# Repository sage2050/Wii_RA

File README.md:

Drop Wii_RA gerbers.zip into JLC pcb  

Components:  

U1 - Seeed Studios XIAO ESP32-S3  
https://www.amazon.com/Dual-core-Supported-Efficiency-Interface-Robotics/dp/B0BYSB66S5?sr=8-3

D1 - OnSemi SS14 or similar  
Optional - allows you to safely power the adapter using the memory card slot while maintaining a usb connection  
https://www.digikey.com/en/products/detail/onsemi/SS14/965474

BZ1 - PUIAudio SMT-0540-T-9-R or similar  
Optional - can play a tone when achievements are earned  
https://www.digikey.com/en/products/detail/pui-audio-inc/SMT-0540-T-9-R/13165909

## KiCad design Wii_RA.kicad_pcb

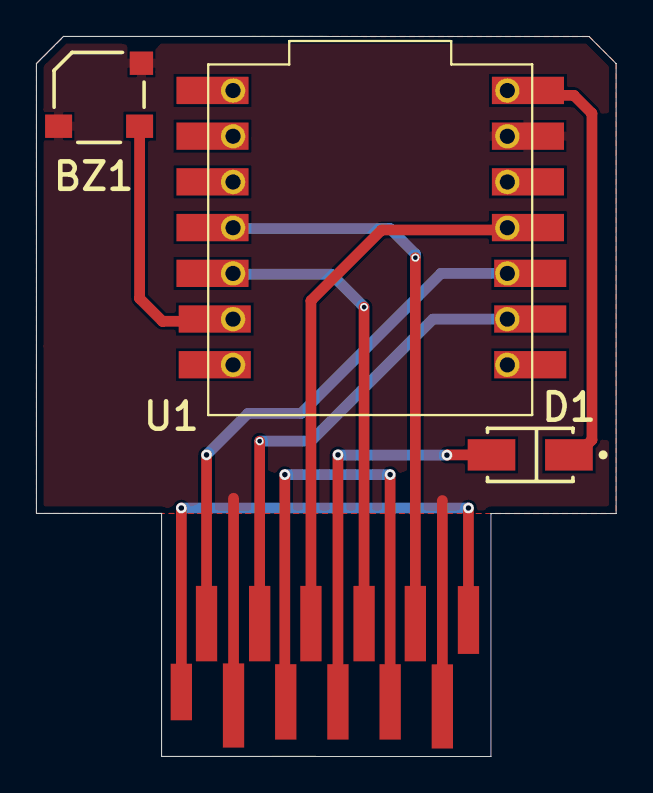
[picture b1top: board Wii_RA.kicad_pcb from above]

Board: 2 copper layers, 32.2 x 40.0 mm, 4 parts (0 on the bottom side), 11 nets.

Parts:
BZ1: SMT-0540-S-R; PUI-SMT-0540-S-R_V
D1: SS14; FP-403AE-MFG
P1: GC_MEMCARD
U1: XIAO-ESP32-C3

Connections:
3V3: P1.4, P1.8
CLK: P1.11, U1.D9
CS: P1.9, U1.D8
EXT: P1.1, P1.12
GC_INT: P1.3, U1.D3
GC_MISO: P1.5, U1.D4
GC_MOSI: P1.7, U1.D10
GND: BZ1.2, BZ1.3, P1.2, P1.10, U1.G
NetBZ1_1: BZ1.1, U1.D5
NetD1_1: D1.1, P1.6
NetD1_2: D1.2, U1.5V
